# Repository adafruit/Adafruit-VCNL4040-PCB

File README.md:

## Adafruit VCNL4040 Proximity and Lux Sensor PCB

<a href="http://www.adafruit.com/products/4161"><br/>
Click here to purchase one from the Adafruit shop</a>

PCB files for the Adafruit VCNL4040 Proximity and Lux Sensor. 

Format is EagleCAD schematic and board layout
* https://www.adafruit.com/product/4161

### Description

The VCNL4040 is a handy two-in-one sensor, with a proximity sensor that works from 0 to 200mm (about 7.5 inches) and light sensor with range of 0.0125 to 6553 lux.

We've all been there. That thing is _close_ but _how close?_ When you need to measure a small distance with reasonable accuracy, such as the rough height of particularly calm bumble bee, the VCNL4040 Proximity Sensor from Vishay can do that for you. If perchance you also needed to measure the amount of light at the same time, perhaps to let the bee to know if it's time for bed, you're in luck! The VCNL4040 can do that too (bumble bee not included, we tried putting it in the anti-static bag but it started buzzing in a threatening manner)

"OK, _finally_ I can get started on my bee measuring and light sensing project, but _how do I use it_?" you say. To make life easier so you can focus on your important work, we've taken the VCNL4040 and put it onto a breakout PCB along with support circuitry to let you use this little wonder with 3.3V (Feather/Raspberry Pi) or 5V (Arduino/ Metro328) logic levels. Additionally since it speaks I2C you can easily connect it up with two wires (plus power and ground!).  We've even included SparkFun qwiic compatible [STEMMA QT](https://learn.adafruit.com/introducing-adafruit-stemma-qt) connectors for the I2C bus so **you don't even need to solder!** [Just wire up to your favorite micro and you can use our CircuitPython/Python or Arduino drivers to easily interface with the VCNL4040 and make approximate approximations of proximity in no time!](https://learn.adafruit.com/adafruit-vcnl4040-proximity-sensor/)

To give you some ability to tune your measurements for your situation, the VCNL4040 lets you adjust the integration time (how long light is being measured) to set the sensitivity of your measurements depending on the lighting conditions. With an integration time of 80ms, since the sensor is only collecting measurements for a short period of time, each measured bit of light represents a larger amount of light. For this reason the maximum range in lux for the 80ms integration time is 6553.5 lux.

If you use a longer integration time and get the same amount of light measurements "events", you know that there is comparatively less light because we're waiting around longer for light to show up and getting the same number, meaning the rate of light events is lower. For this reason at the maximum integration time of 640ms the VCNL4040 will only measure up to 819.2 lux.

It is also worth keeping in mind that as you increase the integration time you are also increasing the sensitivity and resolution within the measurement range

In addition to adjusting the sensitivity of light measurements, you can change the current and duty cycle of the IR LED that powers the proximity detection to adjust how sensitive proximity measurements are
### License

Adafruit invests time and resources providing this open source design, please support Adafruit and open-source hardware by purchasing products from [Adafruit](https://www.adafruit.com)!

Designed by Kattni Rembor for Adafruit Industries.

Creative Commons Attribution/Share-Alike, all text above must be included in any redistribution. 
See license.txt for additional details.

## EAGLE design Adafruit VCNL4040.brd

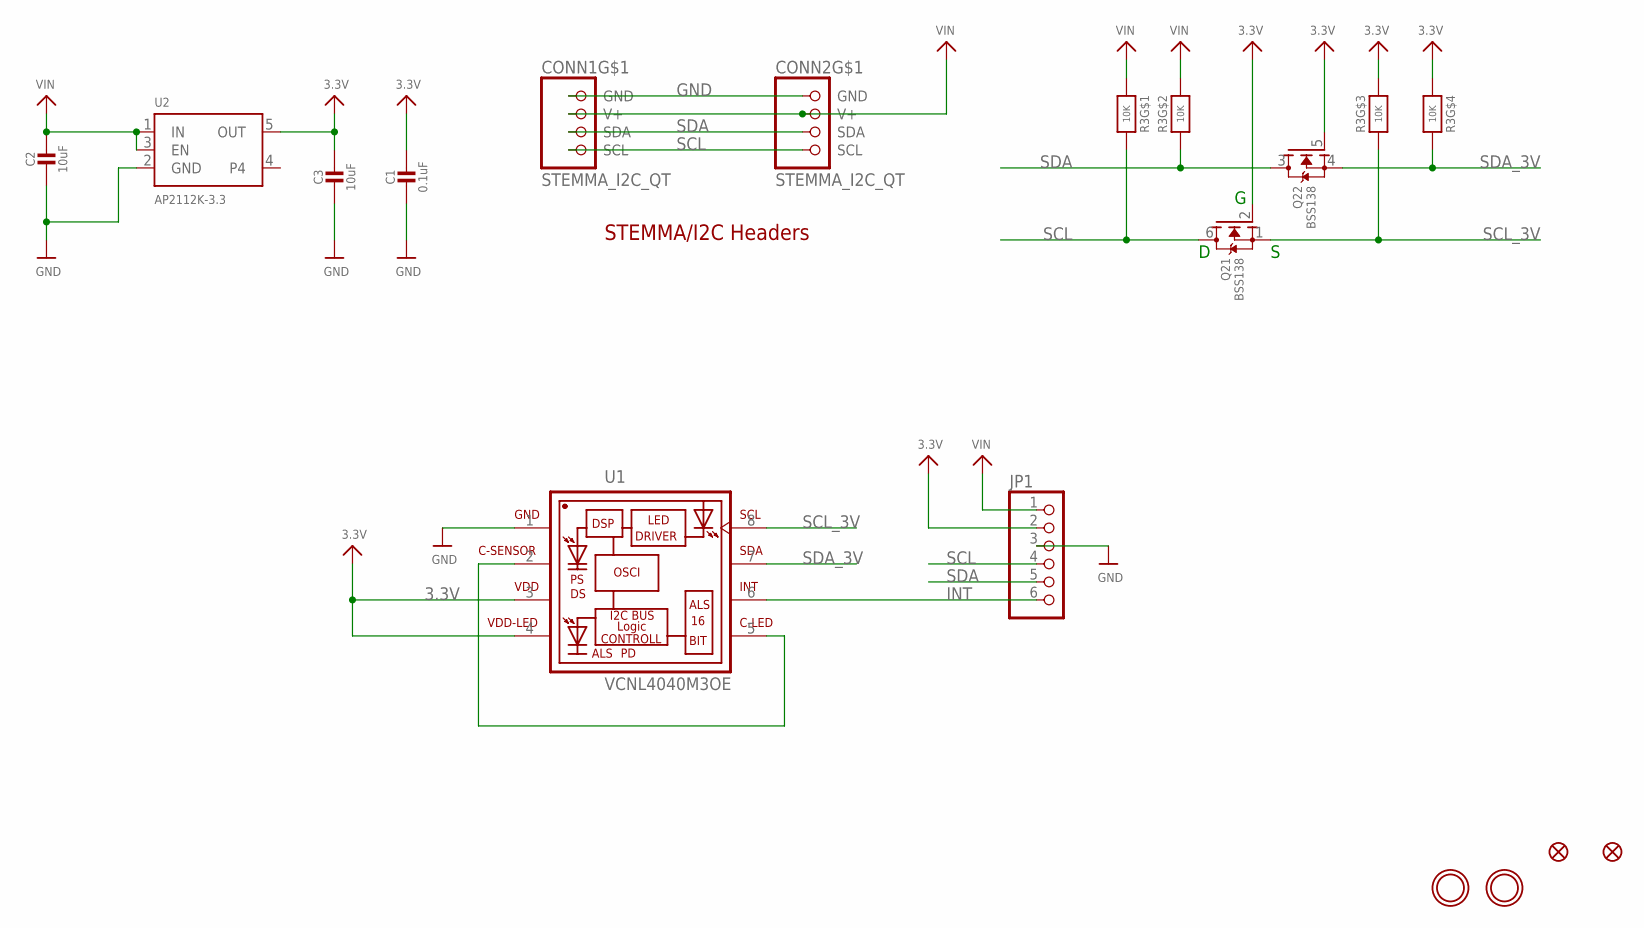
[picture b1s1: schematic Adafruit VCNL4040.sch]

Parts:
C1: 0.1uF; 0603-NO
C2, C3: 10uF; 0805-NO
CONN1, CONN2: STEMMA_I2C_QT; JST_SH4
FID1, FID2: FIDUCIAL_1MM
JP1: HEADER-1X670MIL; 1X06_ROUND_70
Q2: BSS138; SOT363
R3: 10K; RESPACK_4X0603
U1: VCNL4040M3OE; VISHAY_VCNL4040_4X2X1.1
U2: AP2112K-3.3; SOT23-5
U$3, U$4: MOUNTINGHOLE2.5; MOUNTINGHOLE_2.5_PLATED

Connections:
3.3V: C1.1, C3.1, JP1.2, Q2.2 (G), Q2.5 (G), R3.5 (2), R3.6 (2), U1.3 (VDD), U1.4 (VDD-LED), U2.5 (OUT)
CATHODE: U1.2 (C-SENSOR), U1.5 (C-LED)
GND: C1.2, C2.2, C3.2, CONN1.1 (GND), CONN2.1 (GND), JP1.3, U1.1 (GND), U2.2 (GND)
INT: JP1.6, U1.6 (INT)
SCL: CONN1.4 (SCL), CONN2.4 (SCL), JP1.4, Q2.6 (D), R3.8 (2)
SCL_3V: Q2.1 (S), R3.3 (1), U1.8 (SCL)
SDA: CONN1.3 (SDA), CONN2.3 (SDA), JP1.5, Q2.3 (D), R3.7 (2)
SDA_3V: Q2.4 (S), R3.4 (1), U1.7 (SDA)
VIN: C2.1, CONN1.2 (V+), CONN2.2 (V+), JP1.1, R3.1, R3.2 (1), U2.1 (IN), U2.3 (EN)

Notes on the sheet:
STEMMA/I2C Headers

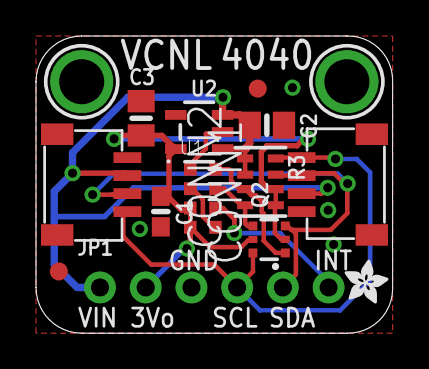
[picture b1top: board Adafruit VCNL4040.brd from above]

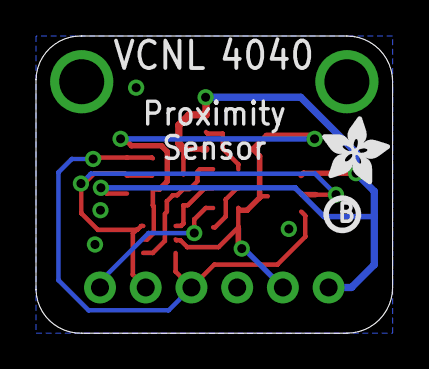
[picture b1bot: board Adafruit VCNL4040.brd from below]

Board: 2 copper layers, 19.8 x 16.5 mm, 17 parts (2 on the bottom side), 9 nets.

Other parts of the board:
U$1: ADAFRUIT_3.5MM
U$8: ADAFRUIT_2.5MM
U$27: PCBFEAT-REV-040

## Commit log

2019-07-10 added readme
2019-08-05 setup with cookiecutter and latest pcb rev.
2019-08-05 fixed copy

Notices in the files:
parts and their libraries:
microbuilder: This work is placed in the public domain, and may be freely used for commercial and non-commercial work with the following conditions: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
